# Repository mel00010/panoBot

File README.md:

# panoBot

## Summary of main responsiblities
- John (OLED display)
- Ben (PID loop)
- Zach (Servo movement/control)
- Justin (Button control)
- Mel (Hardware, main control flow)

## Update Monday March 12th
- Entire directory structure refactored to add some consistency
- Wrote Camera library to control the camera
- Started work on writing main()
- Wrote numerous utility functions as the avr-g++ compiler does not provide any of the C++ standard library headers
- Expanded and updated build system
- Modified build process to enable debugging, and create a target with debugging symbols included.  

## Update Sunday March 11th
- Servo controls for the most part figured out, still need to fine tune timings with hardwarde, but servos now have the ability to update/calculate their angles

- Buttons are finished may need to fine tune the debounce timings as needed, but outputting the correct information

- Screen code started, menu logic is still needed.

- Hardware debugger has arrived and finishing up final hardware configuration, planning on fine tuning with the hardware the upcomming week

- certain moving parts/cases are needing to be printed, planning on doing this Monday 03/12

## Update Sunday March 4th
- Update on project status: Due to hardware issues, the project has been reformed... we are now focusing on the firmware (Interfacing the Arduino board with the physical components: Buttons, toggle switch, servo, led display)

- The board as of Friday March 2 has been updated and is ready to undergo final testing. We now have a proper debugger for the board and can begin testing soft/hardware to ensure it will work properly.

- A PID(Proportion integral derivative) loop has been created to ensure servos will move to the appropriate place

- Button/Toggle switches are 90% done, all code is working (abstractly) but delay timings and port/switch numbers will be fine tuned later.

- Button debounce(noise reduction) implemented through software, this may need to be fine tuned, but will update as needed

- Servo timings have been selected, the prescaler , WGM (Wave Generation Mode) type has been selected 

- Physical display has minimal work, but as the deadline moves closer and members finish we will have multiple people working on the display

- Current goals: Finish rough draft of firmware, test with the board and fine tune timings. 

- Update although Google protobuf was originally planned as part of the project, as a way to interact with the panobot through a laptop, this has been put on hold while we ensure the firmware works properly. If adequate time is left over we will resume working on laptop/panobot interactions

## Update Sunday February 26th

- Spent most of the week working on hardware, the majority of which is complete
- Protobuff created for servo movement , camera communication
- GUI Template done, without buttons, this will be on hold until command line is more refined
(Zach , Ben , Justin, Mel)

## Update Sunday February 18th

- decided on google protobuf syntax/types
- Starting/Stopping 
- Movement:
	Elevation angle, servo angle
- Camera interactions:
	Focus
	Shutter
We all went through the tutorial for protobuf and made sure it is installed correctly/we are all using the correct documentation.

## The circuit board has been designed and built.

## Decided on using GTK+ for GUI, began work on GUI, currently in a rough mockup stage.
(Zach, Ben, Justin , Mel, John)

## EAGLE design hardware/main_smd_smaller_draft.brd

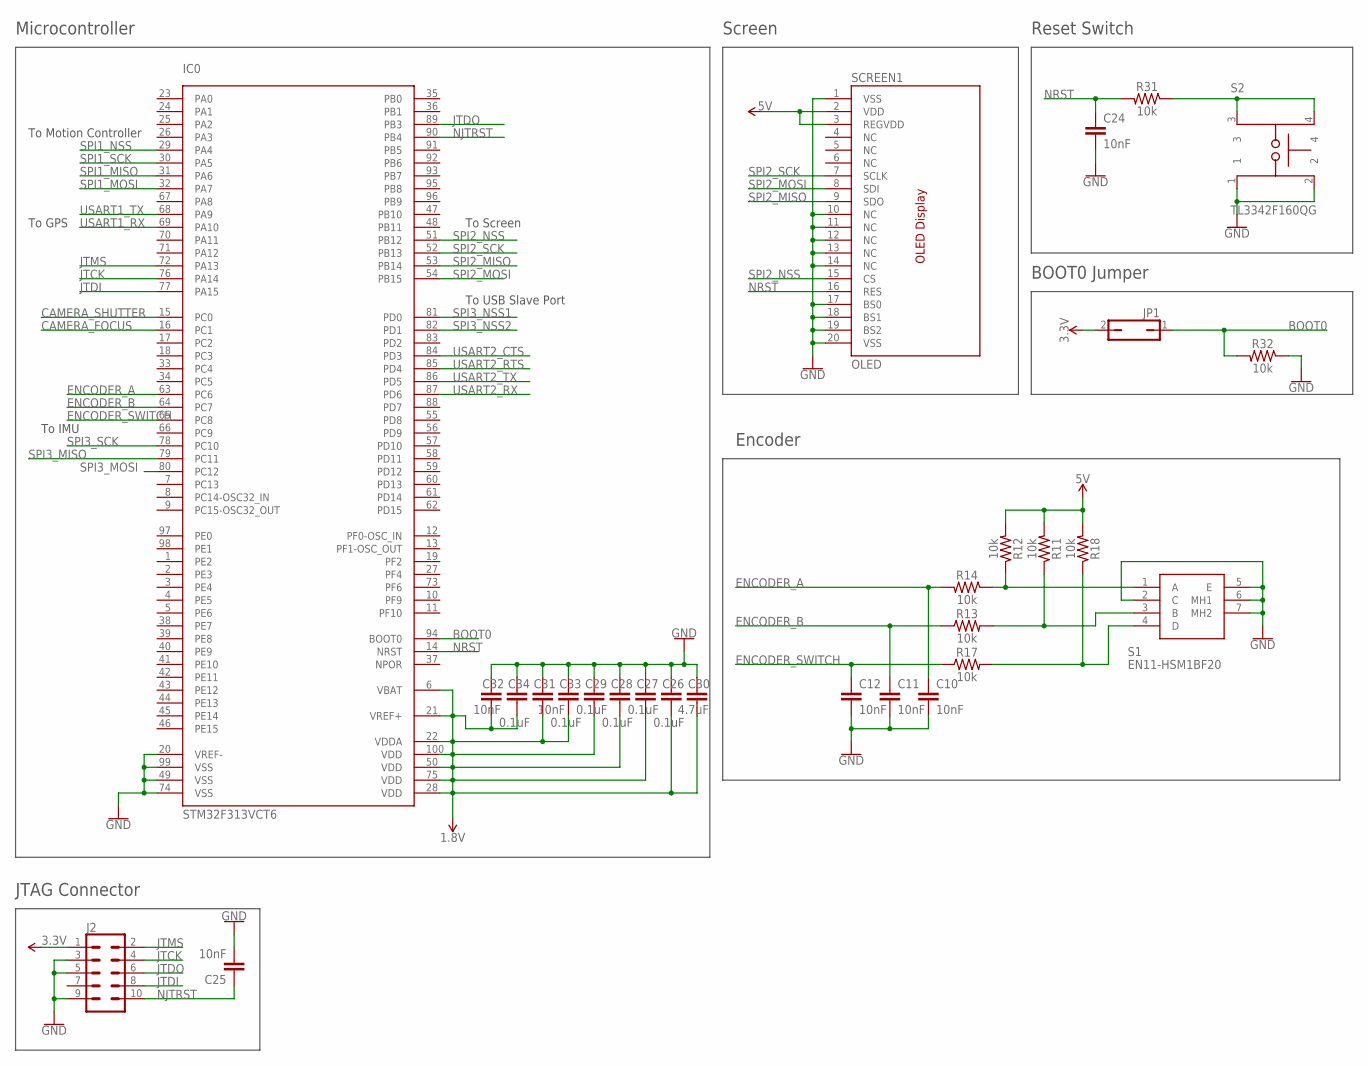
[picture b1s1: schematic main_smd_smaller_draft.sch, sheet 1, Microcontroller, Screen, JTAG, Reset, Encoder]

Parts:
C10, C11, C12, C24, C25, C31, C32: 10nF; 0603
C26, C27, C28, C29: 0.1uF; 0402
C30: 4.7uF; 0603
C33, C34: 0.1uF; 0603
IC0: STM32F313VCT6; QFP50P1600X1600X160-100N
J2: CONN_05X2SHD_LOCK; 2X5-SHROUDED_LOCK
JP1: JP1Q; JP1
R11, R12, R13, R14, R17, R18, R31, R32: 10k; 0603
S1: EN11-HSM1BF20; EN11HSM1BF20
S2: TL3342F160QG; SW_TL3342F160QG
SCREEN1: OLED; SIP-20

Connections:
1.8V: C26.1, C27.1, C28.1, C29.1, C30.1, C31.2, C32.2, C33.2, C34.2, IC0.6 (VBAT), IC0.21 (VREF+), IC0.22 (VDDA), IC0.28 (VDD), IC0.50 (VDD), IC0.75 (VDD), IC0.100 (VDD); also elsewhere on the board
3.3V: J2.1, JP1.2; also elsewhere on the board
5V: R11.2, R12.2, R18.2, SCREEN1.2 (VDD), SCREEN1.3 (REGVDD); also elsewhere on the board
BOOT0: IC0.94 (BOOT0), JP1.1, R32.2
CAMERA_FOCUS: IC0.16 (PC1); also elsewhere on the board
CAMERA_SHUTTER: IC0.15 (PC0); also elsewhere on the board
ENCODER_A: C10.1, IC0.63 (PC6), R14.2
ENCODER_B: C11.1, IC0.64 (PC7), R13.1
ENCODER_SWITCH: C12.1, IC0.65 (PC8), R17.1
GND: C10.2, C11.2, C12.2, C24.2, C25.2, C26.2, C27.2, C28.2, C29.2, C30.2, C31.1, C32.1, C33.1, C34.1, IC0.20 (VREF-), IC0.49 (VSS), IC0.74 (VSS), IC0.99 (VSS), J2.3, J2.5, J2.9, R32.1, S1.2 (C), S1.5 (E), S1.6 (MH1), S1.7 (MH2), S2.1, S2.2, SCREEN1.1 (VSS), SCREEN1.10 (NC), SCREEN1.11 (NC), SCREEN1.12 (NC), SCREEN1.13 (NC), SCREEN1.14 (NC), SCREEN1.17 (BS0), SCREEN1.18 (BS1), SCREEN1.19 (BS2), SCREEN1.20 (VSS); also elsewhere on the board
JTCK: IC0.76 (PA14), J2.4
JTDI: IC0.77 (PA15), J2.8
JTDO: IC0.89 (PB3), J2.6
JTMS: IC0.72 (PA13), J2.2
unnamed: R17.2, R18.1, S1.4 (D)
unnamed: R12.1, R14.1, S1.1 (A)
unnamed: R11.1, R13.2, S1.3 (B)
unnamed: R31.1, S2.3, S2.4
NJTRST: C25.1, IC0.90 (PB4), J2.10
NRST: C24.1, IC0.14 (NRST), R31.2, SCREEN1.16 (RES); also elsewhere on the board
SPI1_MISO: IC0.31 (PA6); also elsewhere on the board
SPI1_MOSI: IC0.32 (PA7); also elsewhere on the board
SPI1_NSS: IC0.29 (PA4); also elsewhere on the board
SPI1_SCK: IC0.30 (PA5); also elsewhere on the board
SPI2_MISO: IC0.53 (PB14), SCREEN1.9 (SDO)
SPI2_MOSI: IC0.54 (PB15), SCREEN1.8 (SDI)
SPI2_NSS: IC0.51 (PB12), SCREEN1.15 (CS)
SPI2_SCK: IC0.52 (PB13), SCREEN1.7 (SCLK)
SPI3_MISO: IC0.79 (PC11); also elsewhere on the board
SPI3_MOSI: IC0.80 (PC12); also elsewhere on the board
SPI3_NSS1: IC0.81 (PD0); also elsewhere on the board
SPI3_NSS2: IC0.82 (PD1); also elsewhere on the board
SPI3_SCK: IC0.78 (PC10); also elsewhere on the board
USART1_RX: IC0.69 (PA10); also elsewhere on the board
USART1_TX: IC0.68 (PA9); also elsewhere on the board
USART2_CTS: IC0.84 (PD3); also elsewhere on the board
USART2_RTS: IC0.85 (PD4); also elsewhere on the board
USART2_RX: IC0.87 (PD6); also elsewhere on the board
USART2_TX: IC0.86 (PD5); also elsewhere on the board

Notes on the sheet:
JTAG Connector
Microcontroller
Screen
Encoder
Reset Switch
BOOT0 Jumper
To Screen
To Motion Controller
To USB Slave Port
To GPS
To IMU

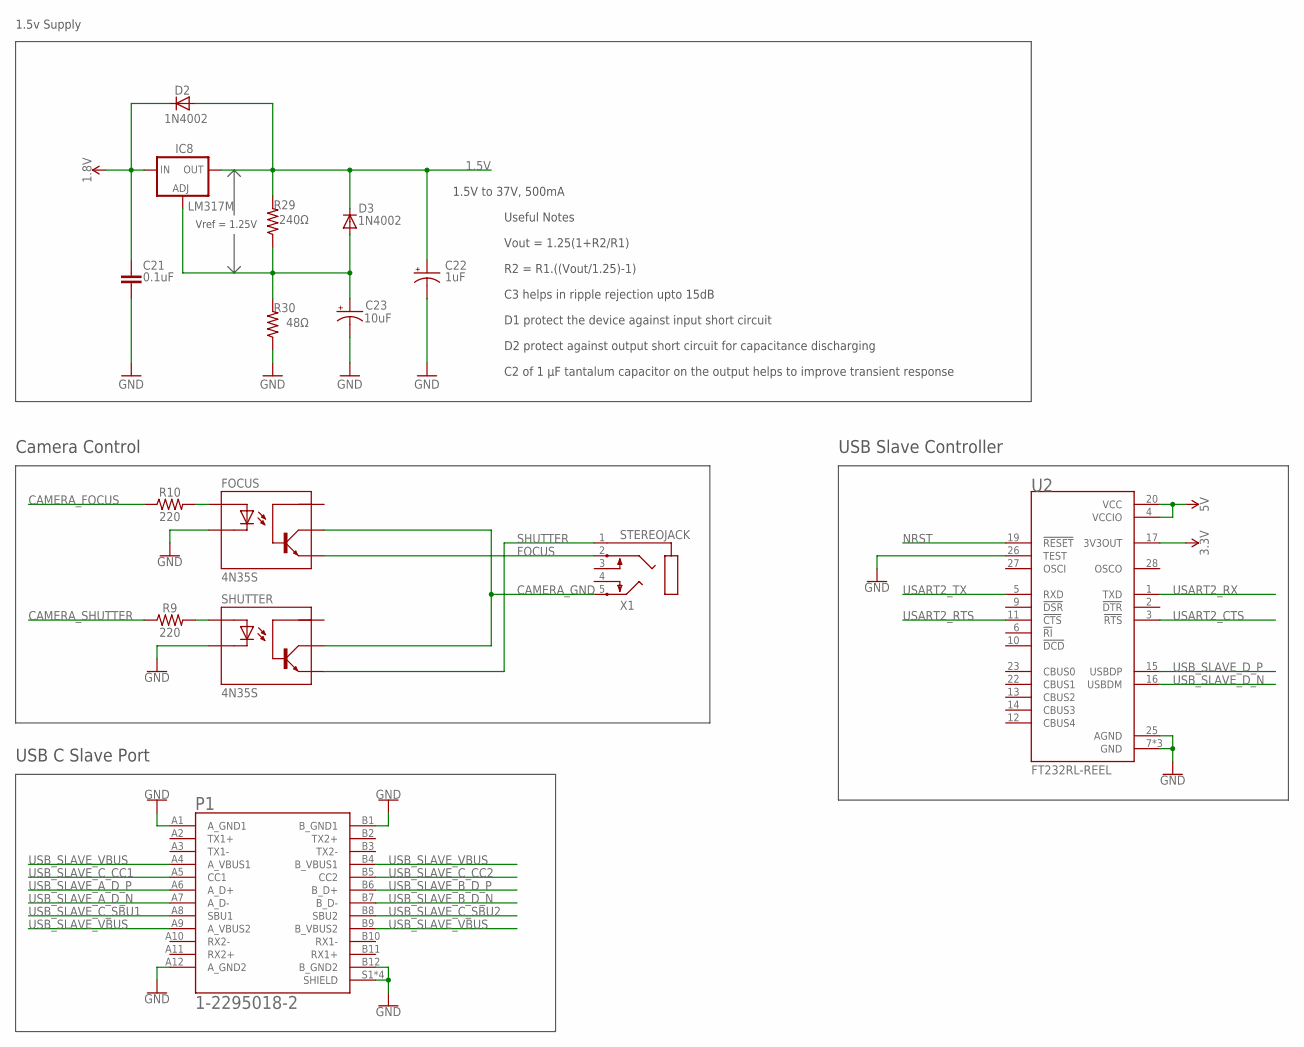
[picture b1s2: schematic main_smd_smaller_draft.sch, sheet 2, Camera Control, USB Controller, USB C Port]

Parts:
C21: 0.1uF; C075-052X106
C22: 1uF; 085CS_1AR
C23: 10uF; 085CS_1AR
D2, D3: 1N4002; DO41-10
FOCUS: 4N35S; SOT23-6
IC8: LM317MBSTT3; SOT223; PARTNUMBER LM317M
P1: 1-2295018-2; TE_1-2295018-2
R9, R10: 220; 0603
R29: 240Ω; M0805
R30: 48Ω; M0805
SHUTTER: 4N35S; SOT23-6
U2: FT232RL-REEL; SOP65P780X200-28N
X1: STEREOJACK; STX3100

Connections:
1.5V: C22.+, D2.A, D3.C, IC8.4 (OUT), R29.2; also elsewhere on the board
1.8V: C21.1, D2.C, IC8.3 (IN); also elsewhere on the board
3.3V: U2.17 (3V3OUT); also elsewhere on the board
5V: U2.4 (VCCIO), U2.20 (VCC); also elsewhere on the board
CAMERA_FOCUS: R10.1; also elsewhere on the board
CAMERA_GND: FOCUS.5, SHUTTER.5, X1.5
CAMERA_SHUTTER: R9.1; also elsewhere on the board
FOCUS: FOCUS.4, X1.2
GND: C21.2, C22.-, C23.-, FOCUS.2, P1.A1 (A_GND1), P1.A12 (A_GND2), P1.B1 (B_GND1), P1.B12 (B_GND2), P1.S1 (SHIELD), P1.S2 (SHIELD), P1.S3 (SHIELD), P1.S4 (SHIELD), R30.1, SHUTTER.2, U2.7 (GND), U2.18 (GND), U2.21 (GND), U2.25 (AGND), U2.26 (TEST); also elsewhere on the board
unnamed: FOCUS.1, R10.2
unnamed: R9.2, SHUTTER.1
unnamed: C23.+, D3.A, IC8.1 (ADJ), R29.1, R30.2
NRST: U2.19 (!RESET); also elsewhere on the board
SHUTTER: SHUTTER.4, X1.1
USART2_CTS: U2.3 (!RTS); also elsewhere on the board
USART2_RTS: U2.11 (!CTS); also elsewhere on the board
USART2_RX: U2.1 (TXD); also elsewhere on the board
USART2_TX: U2.5 (RXD); also elsewhere on the board
USB_SLAVE_A_D_N: P1.A7 (A_D-); also elsewhere on the board
USB_SLAVE_A_D_P: P1.A6 (A_D+); also elsewhere on the board
USB_SLAVE_B_D_N: P1.B7 (B_D-); also elsewhere on the board
USB_SLAVE_B_D_P: P1.B6 (B_D+); also elsewhere on the board
USB_SLAVE_C_CC1: P1.A5 (CC1); also elsewhere on the board
USB_SLAVE_C_CC2: P1.B5 (CC2); also elsewhere on the board
USB_SLAVE_C_SBU1: P1.A8 (SBU1); also elsewhere on the board
USB_SLAVE_C_SBU2: P1.B8 (SBU2); also elsewhere on the board
USB_SLAVE_D_N: U2.16 (USBDM); also elsewhere on the board
USB_SLAVE_D_P: U2.15 (USBDP); also elsewhere on the board
USB_SLAVE_VBUS: P1.A4 (A_VBUS1), P1.A9 (A_VBUS2), P1.B4 (B_VBUS1), P1.B9 (B_VBUS2)

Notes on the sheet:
C3 helps in ripple rejection upto 15dB
D1 protect the device against input short circuit
D2 protect against output short circuit for capacitance discharging
C2 of 1 µF tantalum capacitor on the output helps to improve transient response
Useful Notes
Vref = 1.25V
R2 = R1.((Vout/1.25)-1)
Vout = 1.25(1+R2/R1)
1.5V to 37V, 500mA
1.5v Supply
USB Slave Controller
Camera Control
USB C Slave Port

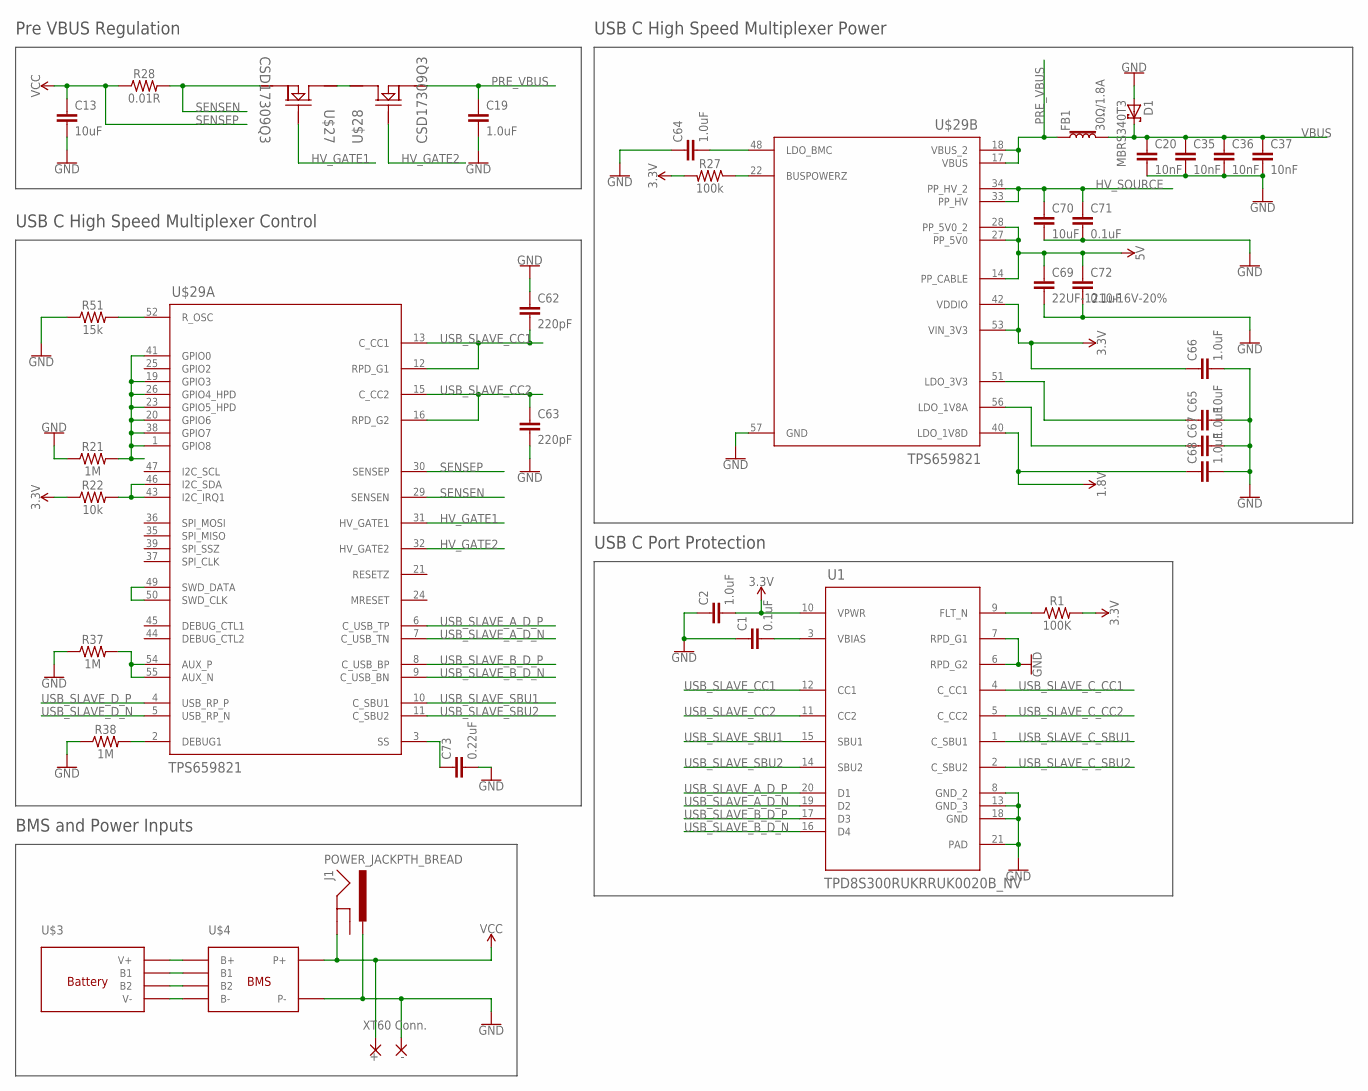
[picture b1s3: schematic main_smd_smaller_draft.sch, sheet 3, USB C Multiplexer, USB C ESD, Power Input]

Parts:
+: 3,81/1,1
-: 3,81/1,1
C1, C71, C72: 0.1uF; 0603
C2: 1.0uF; 0603
C13, C65, C70: 10uF; 1210
C19, C64, C66, C67, C68: 1.0uF; 1206
C20, C35, C36, C37: 10nF; 0603
C62, C63: 220pF; C0402
C69: 22UF-1210-16V-20%; 1210
C73: 0.22uF; 0603
D1: MBRS340T3; SMC
FB1: 30Ω/1.8A; 0603
J1: POWER_JACKPTH_BREAD; POWER_JACK_PTH_BREAD
R1: 100K; 0402
R21, R37, R38: 1M; 0603
R22: 10k; 0603
R27: 100k; 0603
R28: 0.01R; 0805
R51: 15k; 0603
U1: TPD8S300RUKRRUK0020B_NV; RUK0020B_NV
U$27, U$28: CSD17309Q3; DQG0008A
U$29: TPS659821; QFN50P800X800X100-57N

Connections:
1.8V: C68.1, U$29.40 (LDO_1V8D); also elsewhere on the board
3.3V: C2.2, C66.1, R1.2, R22.1, R27.2, U1.10 (VPWR), U$29.42 (VDDIO), U$29.53 (VIN_3V3); also elsewhere on the board
5V: C69.1, C72.1, U$29.14 (PP_CABLE), U$29.27 (PP_5V0), U$29.28 (PP_5V0_2); also elsewhere on the board
GND: -.1, C1.1, C2.1, C13.2, C19.2, C20.2, C35.2, C36.2, C37.2, C62.1, C63.2, C64.1, C65.2, C66.2, C67.2, C68.2, C69.2, C70.2, C71.2, C72.2, C73.2, D1.A, J1.PWR, R21.1, R37.1, R38.1, R51.1, U1.6 (RPD_G2), U1.7 (RPD_G1), U1.8 (GND_2), U1.13 (GND_3), U1.18 (GND), U1.21 (PAD), U$29.57 (GND); also elsewhere on the board
HV_GATE1: U$27.4 (GATE), U$29.31 (HV_GATE1)
HV_GATE2: U$28.4 (GATE), U$29.32 (HV_GATE2)
HV_SOURCE: C70.1, C71.1, U$29.33 (PP_HV), U$29.34 (PP_HV_2); also elsewhere on the board
LDO_3V3: C65.1, U$29.51 (LDO_3V3)
unnamed: R37.2, U$29.54 (AUX_P), U$29.55 (AUX_N)
unnamed: R27.1, U$29.22 (BUSPOWERZ)
unnamed: C64.2, U$29.48 (LDO_BMC)
unnamed: R21.2, U$29.1 (GPIO8), U$29.19 (GPIO3), U$29.20 (GPIO6), U$29.23 (GPIO5_HPD), U$29.26 (GPIO4_HPD), U$29.38 (GPIO7), U$29.41 (GPIO0)
unnamed: U$27.5 (DRAIN_2), U$27.6 (DRAIN_2), U$27.7 (DRAIN_2), U$27.8 (DRAIN_2), U$28.5 (DRAIN_2), U$28.6 (DRAIN_2), U$28.7 (DRAIN_2), U$28.8 (DRAIN_2)
unnamed: U$29.49 (SWD_DATA), U$29.50 (SWD_CLK)
unnamed: R22.2, U$29.43 (I2C_IRQ1), U$29.46 (I2C_SDA)
unnamed: R38.2, U$29.2 (DEBUG1)
unnamed: C73.1, U$29.3 (SS)
unnamed: R51.2, U$29.52 (R_OSC)
unnamed: C67.1, U$29.56 (LDO_1V8A)
unnamed: R1.1, U1.9 (FLT_N)
unnamed: C1.2, U1.3 (VBIAS)
PRE_VBUS: C19.1, FB1.1, U$28.1 (SOURCE_2), U$28.2 (SOURCE_2), U$28.3 (SOURCE_2), U$29.17 (VBUS), U$29.18 (VBUS_2)
SENSEN: R28.2, U$27.1 (SOURCE_2), U$27.2 (SOURCE_2), U$27.3 (SOURCE_2), U$29.29 (SENSEN)
SENSEP: C13.1, R28.1, U$29.30 (SENSEP)
USB_SLAVE_A_D_N: U1.19 (D2), U$29.7 (C_USB_TN); also elsewhere on the board
USB_SLAVE_A_D_P: U1.20 (D1), U$29.6 (C_USB_TP); also elsewhere on the board
USB_SLAVE_B_D_N: U1.16 (D4), U$29.9 (C_USB_BN); also elsewhere on the board
USB_SLAVE_B_D_P: U1.17 (D3), U$29.8 (C_USB_BP); also elsewhere on the board
USB_SLAVE_CC1: C62.2, U1.12 (CC1), U$29.12 (RPD_G1), U$29.13 (C_CC1)
USB_SLAVE_CC2: C63.1, U1.11 (CC2), U$29.15 (C_CC2), U$29.16 (RPD_G2)
USB_SLAVE_C_CC1: U1.4 (C_CC1); also elsewhere on the board
USB_SLAVE_C_CC2: U1.5 (C_CC2); also elsewhere on the board
USB_SLAVE_C_SBU1: U1.1 (C_SBU1); also elsewhere on the board
USB_SLAVE_C_SBU2: U1.2 (C_SBU2); also elsewhere on the board
USB_SLAVE_D_N: U$29.5 (USB_RP_N); also elsewhere on the board
USB_SLAVE_D_P: U$29.4 (USB_RP_P); also elsewhere on the board
USB_SLAVE_SBU1: U1.15 (SBU1), U$29.10 (C_SBU1)
USB_SLAVE_SBU2: U1.14 (SBU2), U$29.11 (C_SBU2)
VBUS: C20.1, C35.1, C36.1, C37.1, D1.C, FB1.2
VCC: +.1, J1.GND; also elsewhere on the board

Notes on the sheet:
Pre VBUS Regulation
USB C High Speed Multiplexer Control
USB C High Speed Multiplexer Power
XT60 Conn.
BMS and Power Inputs
USB C Port Protection

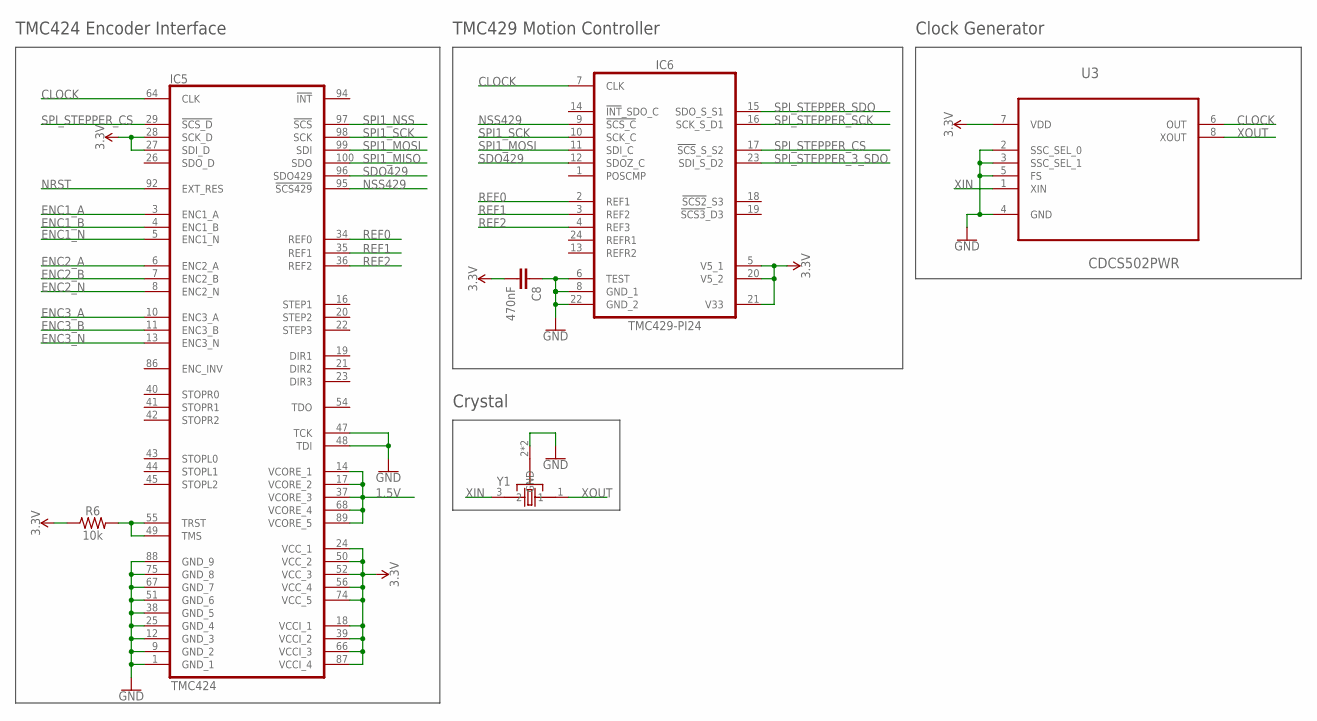
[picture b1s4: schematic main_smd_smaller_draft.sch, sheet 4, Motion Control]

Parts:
C8: 470nF; 0402
IC5: TMC424; TMC_TQFP100_0.5_14X14
IC6: TMC429-PI24; TMC_SO24_SOT137-1_1.27_15.5X7.5
R6: 10k; 0603
U3: CDCS502PWR; SOP65P640X120-8N
Y1: 7B-16.000MAAJ-T; 7B-16.000MAAJ-T_OSCSC500X320X105-4N

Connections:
1.5V: IC5.14 (VCORE_1), IC5.17 (VCORE_2), IC5.37 (VCORE_3), IC5.68 (VCORE_4), IC5.89 (VCORE_5); also elsewhere on the board
3.3V: C8.2, IC5.18 (VCCI_1), IC5.24 (VCC_1), IC5.27 (SDI_D), IC5.28 (SCK_D), IC5.39 (VCCI_2), IC5.50 (VCC_2), IC5.52 (VCC_3), IC5.56 (VCC_4), IC5.66 (VCCI_3), IC5.74 (VCC_5), IC5.87 (VCCI_4), IC6.5 (V5_1), IC6.20 (V5_2), IC6.21 (V33), R6.1, U3.7 (VDD); also elsewhere on the board
CLOCK: IC5.64 (CLK), IC6.7 (CLK), U3.6 (OUT); also elsewhere on the board
ENC1_A: IC5.3 (ENC1_A); also elsewhere on the board
ENC1_B: IC5.4 (ENC1_B); also elsewhere on the board
ENC1_N: IC5.5 (ENC1_N); also elsewhere on the board
ENC2_A: IC5.6 (ENC2_A); also elsewhere on the board
ENC2_B: IC5.7 (ENC2_B); also elsewhere on the board
ENC2_N: IC5.8 (ENC2_N); also elsewhere on the board
ENC3_A: IC5.10 (ENC3_A); also elsewhere on the board
ENC3_B: IC5.11 (ENC3_B); also elsewhere on the board
ENC3_N: IC5.13 (ENC3_N); also elsewhere on the board
GND: C8.1, IC5.1 (GND_1), IC5.9 (GND_2), IC5.12 (GND_3), IC5.25 (GND_4), IC5.38 (GND_5), IC5.47 (TCK), IC5.48 (TDI), IC5.51 (GND_6), IC5.67 (GND_7), IC5.75 (GND_8), IC5.88 (GND_9), IC6.6 (TEST), IC6.8 (GND_1), IC6.22 (GND_2), U3.2 (SSC_SEL_0), U3.3 (SSC_SEL_1), U3.4 (GND), U3.5 (FS), Y1.2 (GND), Y1.4 (GND); also elsewhere on the board
unnamed: IC5.49 (TMS), IC5.55 (TRST), R6.2
NRST: IC5.92 (EXT_RES); also elsewhere on the board
NSS429: IC5.95 (!SCS429), IC6.9 (!SCS_C)
REF0: IC5.34 (REF0), IC6.2 (REF1)
REF1: IC5.35 (REF1), IC6.3 (REF2)
REF2: IC5.36 (REF2), IC6.4 (REF3)
SDO429: IC5.96 (SDO429), IC6.12 (SDOZ_C)
SPI1_MISO: IC5.100 (SDO); also elsewhere on the board
SPI1_MOSI: IC5.99 (SDI), IC6.11 (SDI_C); also elsewhere on the board
SPI1_NSS: IC5.97 (!SCS); also elsewhere on the board
SPI1_SCK: IC5.98 (SCK), IC6.10 (SCK_C); also elsewhere on the board
SPI_STEPPER_3_SDO: IC6.23 (SDI_S_D2); also elsewhere on the board
SPI_STEPPER_CS: IC5.29 (!SCS_D), IC6.17 (!SCS!_S_S2); also elsewhere on the board
SPI_STEPPER_SCK: IC6.16 (SCK_S_D1); also elsewhere on the board
SPI_STEPPER_SDO: IC6.15 (SDO_S_S1); also elsewhere on the board
XIN: U3.1 (XIN), Y1.3 (2)
XOUT: U3.8 (XOUT), Y1.1

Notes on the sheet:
TMC424 Encoder Interface
TMC429 Motion Controller
Crystal
Clock Generator

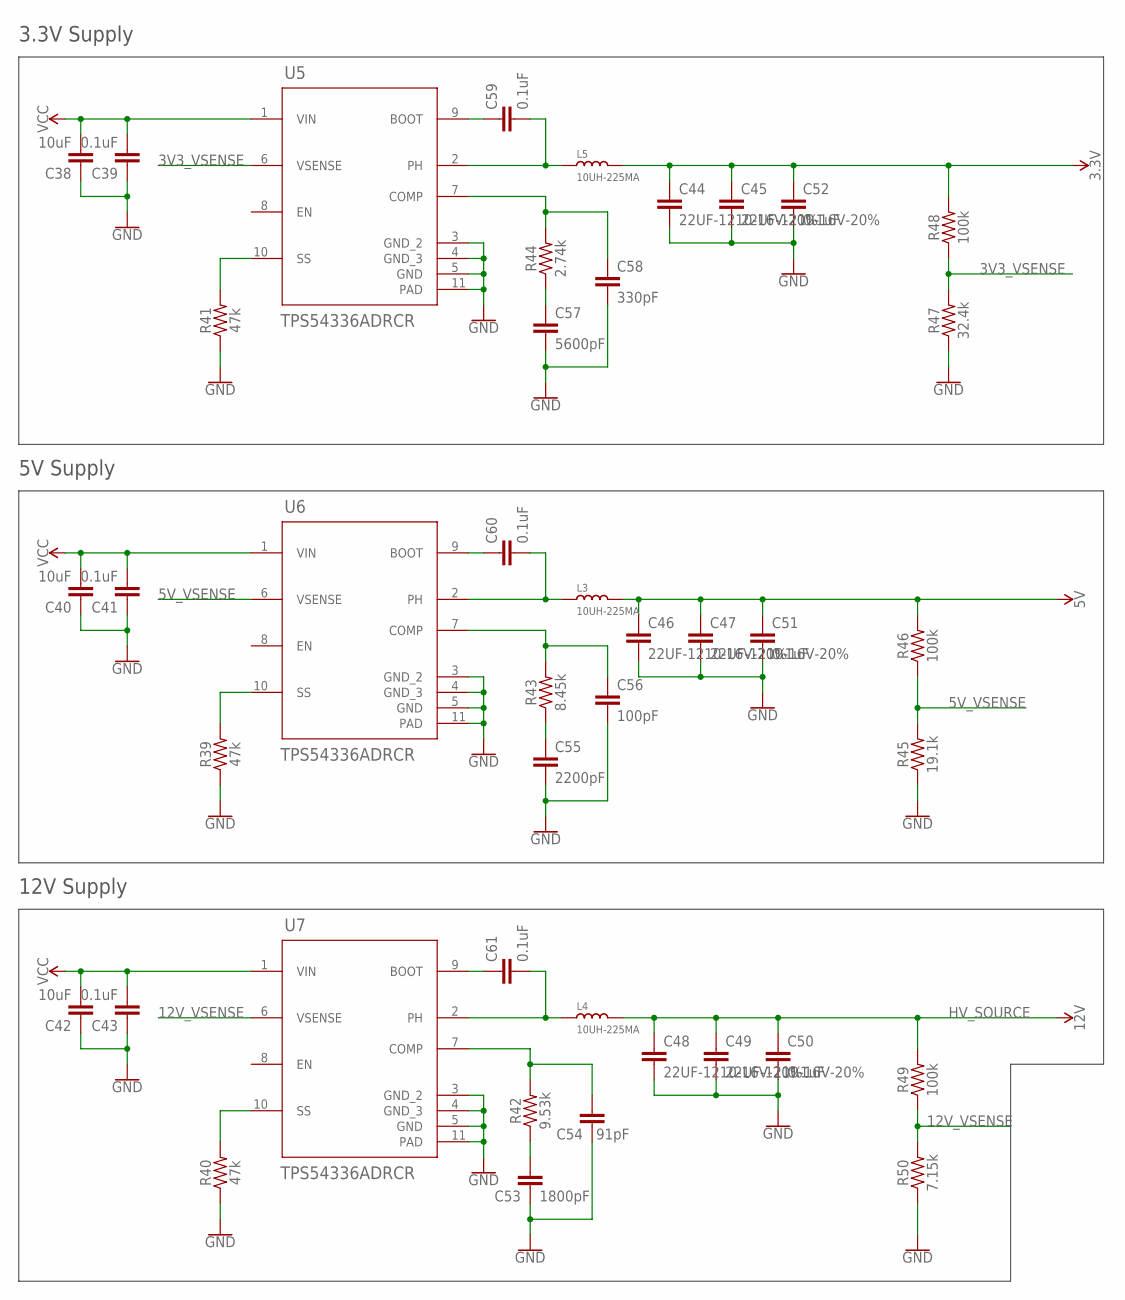
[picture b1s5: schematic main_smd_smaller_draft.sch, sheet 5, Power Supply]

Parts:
C38, C40, C42: 10uF; 1210
C39, C41, C43, C59, C60, C61: 0.1uF; 0603
C44, C45, C46, C47, C48, C49: 22UF-1210-16V-20%; 1210
C50, C51, C52: 0.1uF; 0402
C53: 1800pF; C0402
C54: 91pF; C0402
C55: 2200pF; C0402
C56: 100pF; C0402
C57: 5600pF; C0402
C58: 330pF; C0402
L3, L4, L5: 10UH-225MA; L0806
R39, R40, R41: 47k; 0603
R42: 9.53k; 0603
R43: 8.45k; 0603
R44: 2.74k; 0603
R45: 19.1k; 0603
R46, R48, R49: 100k; 0603
R47: 32.4k; 0603
R50: 7.15k; 0603
U5, U6, U7: TPS54336ADRCR; DRC0010J

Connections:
3.3V: C44.1, C45.1, C52.1, L5.2, R48.2; also elsewhere on the board
3V3_VSENSE: R47.2, R48.1, U5.6 (VSENSE)
5V: C46.1, C47.1, C51.1, L3.2, R46.2; also elsewhere on the board
5V_VSENSE: R45.2, R46.1, U6.6 (VSENSE)
12V_VSENSE: R49.1, R50.2, U7.6 (VSENSE)
GND: C38.1, C39.1, C40.1, C41.1, C42.1, C43.1, C44.2, C45.2, C46.2, C47.2, C48.2, C49.2, C50.2, C51.2, C52.2, C53.1, C54.1, C55.2, C56.2, C57.2, C58.2, R39.1, R40.1, R41.1, R45.1, R47.1, R50.1, U5.3 (GND_2), U5.4 (GND_3), U5.5 (GND), U5.11 (PAD), U6.3 (GND_2), U6.4 (GND_3), U6.5 (GND), U6.11 (PAD), U7.3 (GND_2), U7.4 (GND_3), U7.5 (GND), U7.11 (PAD); also elsewhere on the board
HV_SOURCE: C48.1, C49.1, C50.1, L4.2, R49.2; also elsewhere on the board
unnamed: R41.2, U5.10 (SS)
unnamed: R39.2, U6.10 (SS)
unnamed: R40.2, U7.10 (SS)
unnamed: C61.2, L4.1, U7.2 (PH)
unnamed: C60.2, L3.1, U6.2 (PH)
unnamed: C59.2, L5.1, U5.2 (PH)
unnamed: C61.1, U7.9 (BOOT)
unnamed: C59.1, U5.9 (BOOT)
unnamed: C60.1, U6.9 (BOOT)
unnamed: C53.2, R42.1
unnamed: C54.2, R42.2, U7.7 (COMP)
unnamed: C55.1, R43.1
unnamed: C56.1, R43.2, U6.7 (COMP)
unnamed: C57.1, R44.1
unnamed: C58.1, R44.2, U5.7 (COMP)
VCC: C38.2, C39.2, C40.2, C41.2, C42.2, C43.2, U5.1 (VIN), U6.1 (VIN), U7.1 (VIN); also elsewhere on the board

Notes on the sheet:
3.3V Supply
5V Supply
12V Supply

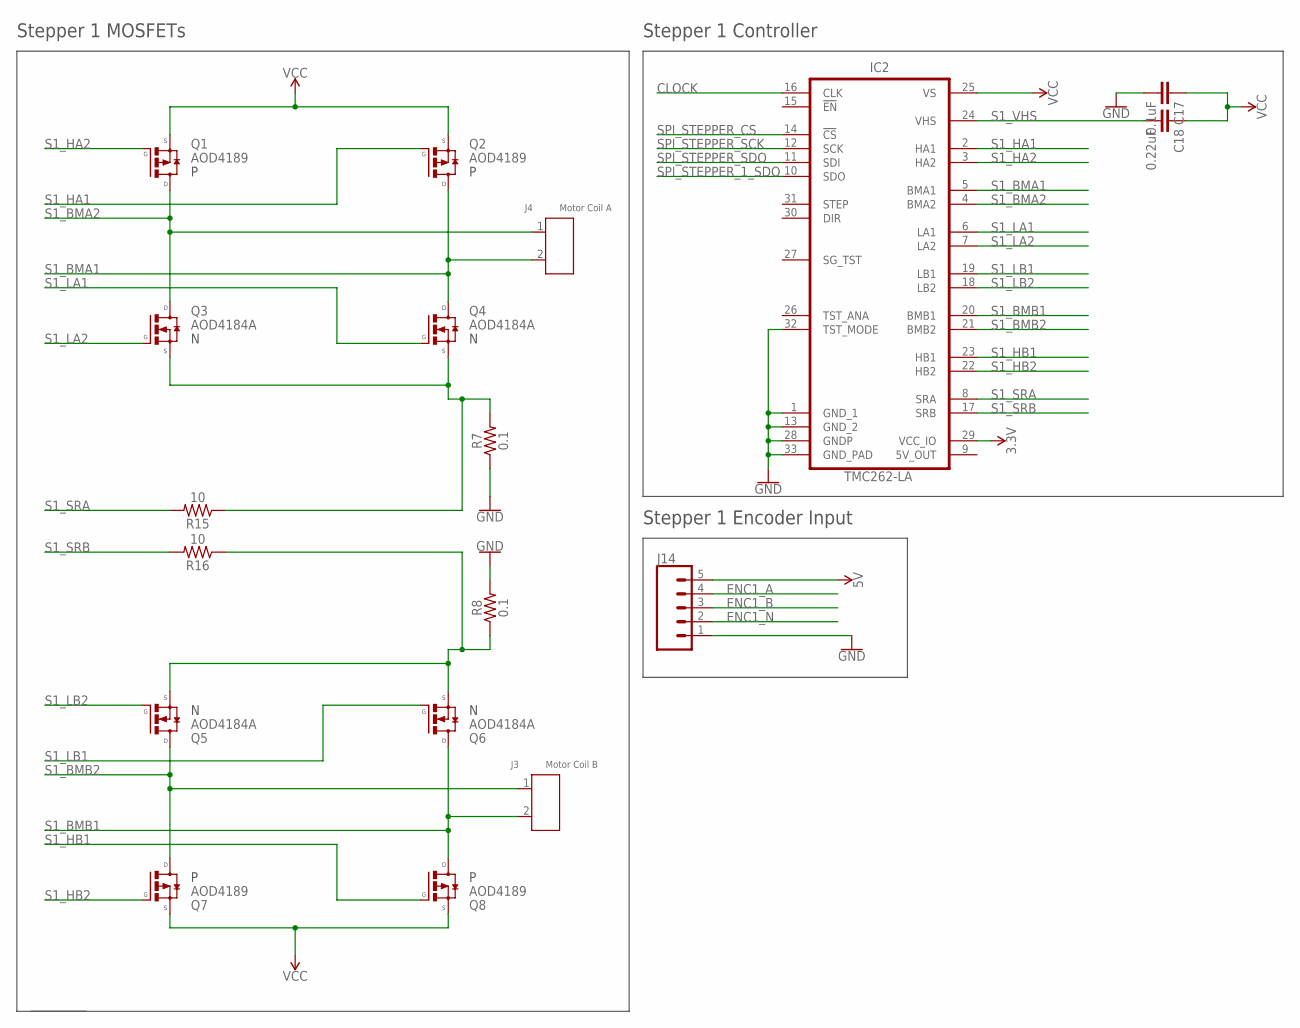
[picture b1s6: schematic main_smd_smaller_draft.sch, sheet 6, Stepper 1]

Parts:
C17: 0.1uF; 0402
C18: 0.22uF; 0603
IC2: TMC262-LA; TMC_QFN32_0.5_5.0X5.0
J3: Motor Coil B; H2-5.0-10.5X8.0MM
J4: Motor Coil A; H2-5.0-10.5X8.0MM
J14: CONN_05; 1X05
Q1, Q2, Q7, Q8: AOD4189; TO252
Q3, Q4, Q5, Q6: AOD4184A; TO252
R7, R8: 0.1; 1210
R15, R16: 10; 1206

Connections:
3.3V: IC2.29 (VCC_IO); also elsewhere on the board
5V: J14.5; also elsewhere on the board
CLOCK: IC2.16 (CLK); also elsewhere on the board
ENC1_A: J14.4; also elsewhere on the board
ENC1_B: J14.3; also elsewhere on the board
ENC1_N: J14.2; also elsewhere on the board
GND: C17.2, IC2.1 (GND_1), IC2.13 (GND_2), IC2.28 (GNDP), IC2.32 (TST_MODE), IC2.33 (GND_PAD), J14.1, R7.1, R8.2; also elsewhere on the board
unnamed: Q5.R (S), Q6.R (S), R8.1, R16.1
unnamed: Q3.R (S), Q4.R (S), R7.2, R15.1
S1_BMA1: IC2.5 (BMA1), J4.2, Q2.C (D), Q4.C (D)
S1_BMA2: IC2.4 (BMA2), J4.1, Q1.C (D), Q3.C (D)
S1_BMB1: IC2.20 (BMB1), J3.2, Q6.C (D), Q8.C (D)
S1_BMB2: IC2.21 (BMB2), J3.1, Q5.C (D), Q7.C (D)
S1_HA1: IC2.2 (HA1), Q2.L (G)
S1_HA2: IC2.3 (HA2), Q1.L (G)
S1_HB1: IC2.23 (HB1), Q8.L (G)
S1_HB2: IC2.22 (HB2), Q7.L (G)
S1_LA1: IC2.6 (LA1), Q4.L (G)
S1_LA2: IC2.7 (LA2), Q3.L (G)
S1_LB1: IC2.19 (LB1), Q6.L (G)
S1_LB2: IC2.18 (LB2), Q5.L (G)
S1_SRA: IC2.8 (SRA), R15.2
S1_SRB: IC2.17 (SRB), R16.2
S1_VHS: C18.2, IC2.24 (VHS)
SPI_STEPPER_1_SDO: IC2.10 (SDO); also elsewhere on the board
SPI_STEPPER_CS: IC2.14 (!CS!); also elsewhere on the board
SPI_STEPPER_SCK: IC2.12 (SCK); also elsewhere on the board
SPI_STEPPER_SDO: IC2.11 (SDI); also elsewhere on the board
VCC: C17.1, C18.1, IC2.25 (VS), Q1.R (S), Q2.R (S), Q7.R (S), Q8.R (S); also elsewhere on the board

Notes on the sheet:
Stepper 1 MOSFETs
Stepper 1 Controller
Stepper 1 Encoder Input

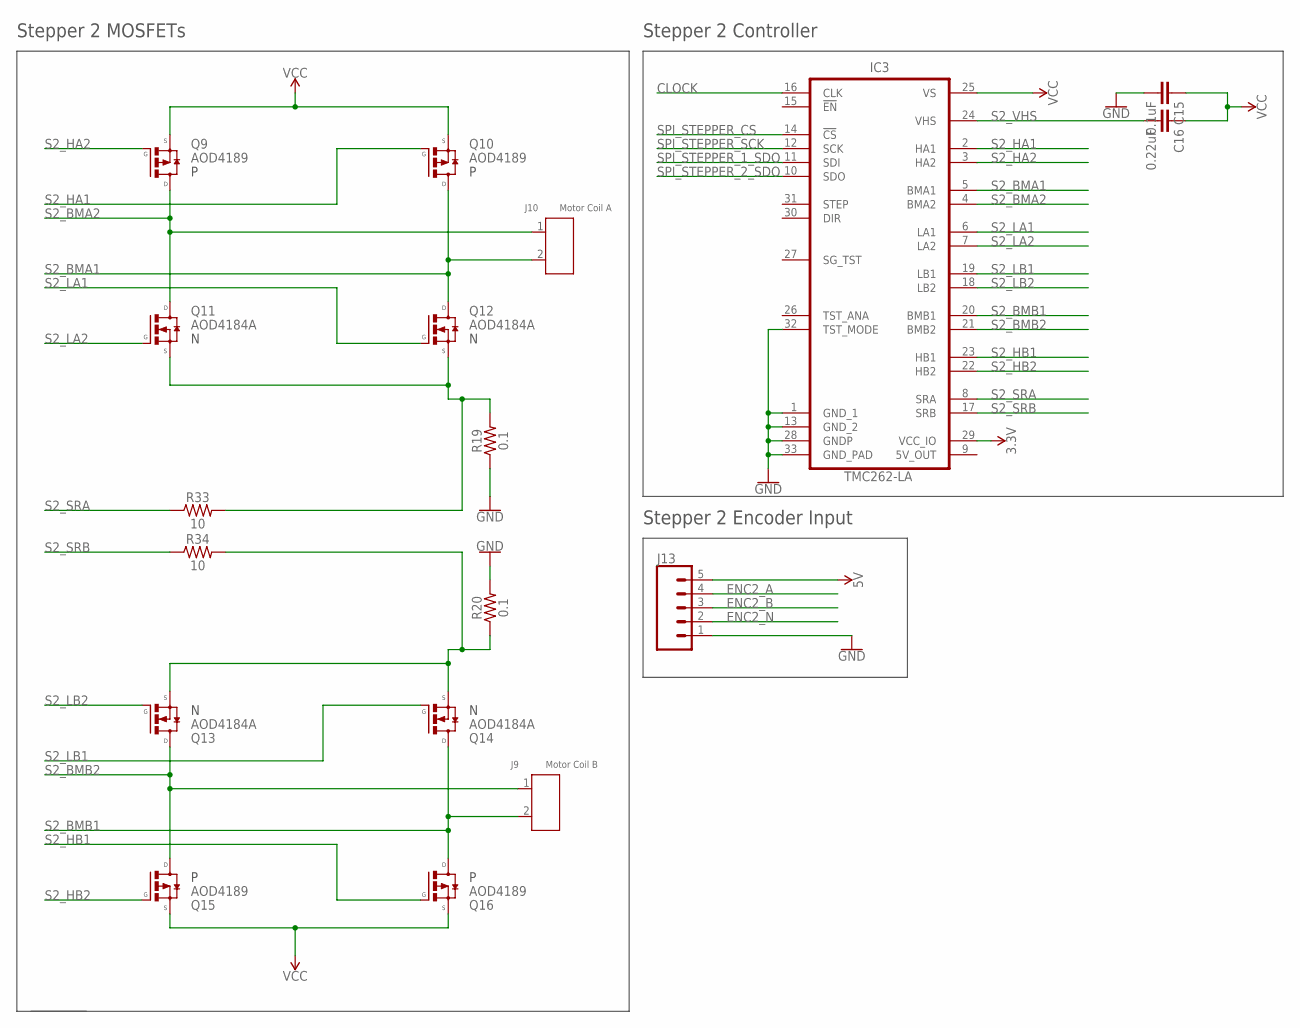
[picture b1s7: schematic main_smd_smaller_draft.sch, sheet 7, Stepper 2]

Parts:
C15: 0.1uF; 0402
C16: 0.22uF; 0603
IC3: TMC262-LA; TMC_QFN32_0.5_5.0X5.0
J9: Motor Coil B; H2-5.0-10.5X8.0MM
J10: Motor Coil A; H2-5.0-10.5X8.0MM
J13: CONN_05; 1X05
Q9, Q10, Q15, Q16: AOD4189; TO252
Q11, Q12, Q13, Q14: AOD4184A; TO252
R19, R20: 0.1; 1210
R33, R34: 10; 1206

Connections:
3.3V: IC3.29 (VCC_IO); also elsewhere on the board
5V: J13.5; also elsewhere on the board
CLOCK: IC3.16 (CLK); also elsewhere on the board
ENC2_A: J13.4; also elsewhere on the board
ENC2_B: J13.3; also elsewhere on the board
ENC2_N: J13.2; also elsewhere on the board
GND: C15.2, IC3.1 (GND_1), IC3.13 (GND_2), IC3.28 (GNDP), IC3.32 (TST_MODE), IC3.33 (GND_PAD), J13.1, R19.1, R20.2; also elsewhere on the board
unnamed: Q11.R (S), Q12.R (S), R19.2, R33.2
unnamed: Q13.R (S), Q14.R (S), R20.1, R34.2
S2_BMA1: IC3.5 (BMA1), J10.2, Q10.C (D), Q12.C (D)
S2_BMA2: IC3.4 (BMA2), J10.1, Q9.C (D), Q11.C (D)
S2_BMB1: IC3.20 (BMB1), J9.2, Q14.C (D), Q16.C (D)
S2_BMB2: IC3.21 (BMB2), J9.1, Q13.C (D), Q15.C (D)
S2_HA1: IC3.2 (HA1), Q10.L (G)
S2_HA2: IC3.3 (HA2), Q9.L (G)
S2_HB1: IC3.23 (HB1), Q16.L (G)
S2_HB2: IC3.22 (HB2), Q15.L (G)
S2_LA1: IC3.6 (LA1), Q12.L (G)
S2_LA2: IC3.7 (LA2), Q11.L (G)
S2_LB1: IC3.19 (LB1), Q14.L (G)
S2_LB2: IC3.18 (LB2), Q13.L (G)
S2_SRA: IC3.8 (SRA), R33.1
S2_SRB: IC3.17 (SRB), R34.1
S2_VHS: C16.2, IC3.24 (VHS)
SPI_STEPPER_1_SDO: IC3.11 (SDI); also elsewhere on the board
SPI_STEPPER_2_SDO: IC3.10 (SDO); also elsewhere on the board
SPI_STEPPER_CS: IC3.14 (!CS!); also elsewhere on the board
SPI_STEPPER_SCK: IC3.12 (SCK); also elsewhere on the board
VCC: C15.1, C16.1, IC3.25 (VS), Q9.R (S), Q10.R (S), Q15.R (S), Q16.R (S); also elsewhere on the board

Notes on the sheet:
Stepper 2 MOSFETs
Stepper 2 Controller
Stepper 2 Encoder Input

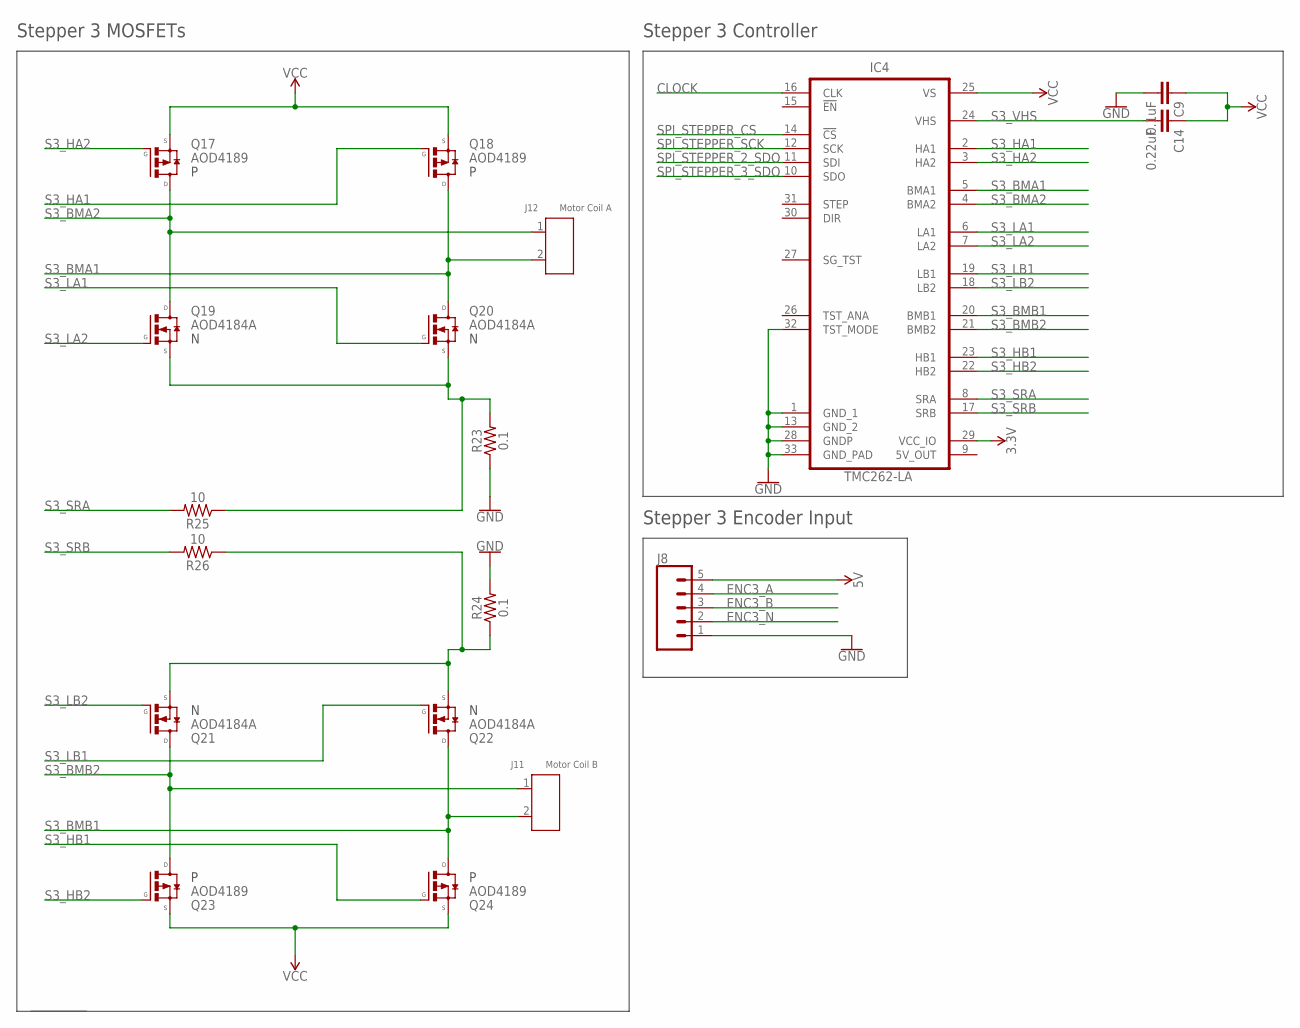
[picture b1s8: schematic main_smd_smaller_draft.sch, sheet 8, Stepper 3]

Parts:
C9: 0.1uF; 0402
C14: 0.22uF; 0603
IC4: TMC262-LA; TMC_QFN32_0.5_5.0X5.0
J8: CONN_05; 1X05
J11: Motor Coil B; H2-5.0-10.5X8.0MM
J12: Motor Coil A; H2-5.0-10.5X8.0MM
Q17, Q18, Q23, Q24: AOD4189; TO252
Q19, Q20, Q21, Q22: AOD4184A; TO252
R23, R24: 0.1; 1210
R25, R26: 10; 1206

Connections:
3.3V: IC4.29 (VCC_IO); also elsewhere on the board
5V: J8.5; also elsewhere on the board
CLOCK: IC4.16 (CLK); also elsewhere on the board
ENC3_A: J8.4; also elsewhere on the board
ENC3_B: J8.3; also elsewhere on the board
ENC3_N: J8.2; also elsewhere on the board
GND: C9.2, IC4.1 (GND_1), IC4.13 (GND_2), IC4.28 (GNDP), IC4.32 (TST_MODE), IC4.33 (GND_PAD), J8.1, R23.1, R24.2; also elsewhere on the board
unnamed: Q19.R (S), Q20.R (S), R23.2, R25.1
unnamed: Q21.R (S), Q22.R (S), R24.1, R26.1
S3_BMA1: IC4.5 (BMA1), J12.2, Q18.C (D), Q20.C (D)
S3_BMA2: IC4.4 (BMA2), J12.1, Q17.C (D), Q19.C (D)
S3_BMB1: IC4.20 (BMB1), J11.2, Q22.C (D), Q24.C (D)
S3_BMB2: IC4.21 (BMB2), J11.1, Q21.C (D), Q23.C (D)
S3_HA1: IC4.2 (HA1), Q18.L (G)
S3_HA2: IC4.3 (HA2), Q17.L (G)
S3_HB1: IC4.23 (HB1), Q24.L (G)
S3_HB2: IC4.22 (HB2), Q23.L (G)
S3_LA1: IC4.6 (LA1), Q20.L (G)
S3_LA2: IC4.7 (LA2), Q19.L (G)
S3_LB1: IC4.19 (LB1), Q22.L (G)
S3_LB2: IC4.18 (LB2), Q21.L (G)
S3_SRA: IC4.8 (SRA), R25.2
S3_SRB: IC4.17 (SRB), R26.2
S3_VHS: C14.2, IC4.24 (VHS)
SPI_STEPPER_2_SDO: IC4.11 (SDI); also elsewhere on the board
SPI_STEPPER_3_SDO: IC4.10 (SDO); also elsewhere on the board
SPI_STEPPER_CS: IC4.14 (!CS!); also elsewhere on the board
SPI_STEPPER_SCK: IC4.12 (SCK); also elsewhere on the board
VCC: C9.1, C14.1, IC4.25 (VS), Q17.R (S), Q18.R (S), Q23.R (S), Q24.R (S); also elsewhere on the board

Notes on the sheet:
Stepper 3 MOSFETs
Stepper 3 Controller
Stepper 3 Encoder Input

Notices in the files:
hardware/main_smd_smaller_draft.brd:
Copyright Mel McCalla
All rights reserved
parts and their libraries:
SparkFun-Connectors: Licensing: Creative Commons ShareAlike 4.0 International - https://creativecommons.org/licenses/by-sa/4.0
SparkFun-Aesthetics: Released under the Creative Commons Attribution Share-Alike 4.0 License
SparkFun-Aesthetics: https://creativecommons.org/licenses/by-sa/4.0
